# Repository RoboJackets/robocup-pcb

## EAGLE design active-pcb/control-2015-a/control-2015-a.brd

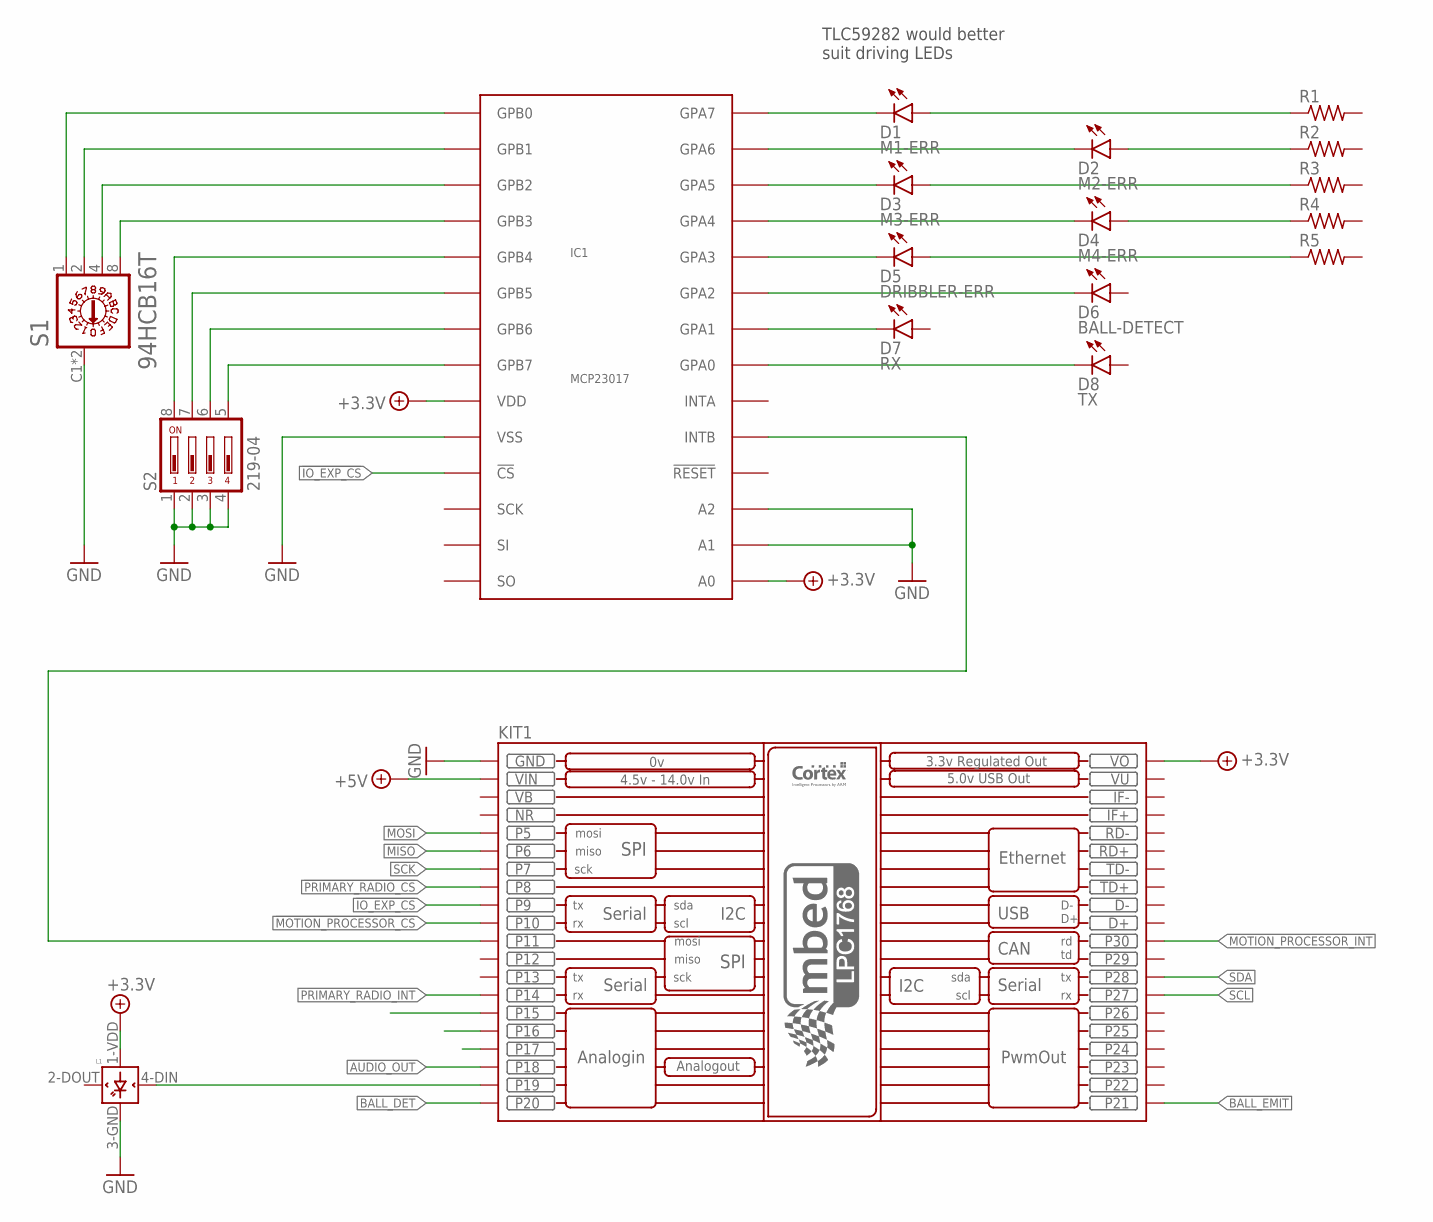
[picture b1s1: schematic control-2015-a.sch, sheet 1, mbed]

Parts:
D1: M1-ERR; LED-0603
D2: M2-ERR; LED-0603
D3: M3-ERR; LED-0603
D4: M4-ERR; LED-0603
D5: DRIBBLER-ERR; LED-0603
D6: BALL-DETECT; LED-0603
D7: RX; LED-0603
D8: TX; LED-0603
IC1: MCP23017; SSOP-28
KIT1: MBED_NXP_LPC1768; MBED-KIT
L1: WS2812B
R1, R2, R3, R4, R5: R-US_R0402; R0402
S1: 94HCB16T; HEX
S2: 219-04; CTS-219-04

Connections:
!IO_EXP_CS!: IC1.11 (!CS!), KIT1.P$9 (P9)
!MOTION_PROCESSOR_CS!: KIT1.P$10 (P10); also elsewhere on the board
!PRIMARY_RADIO_CS!: KIT1.P$8 (P8); also elsewhere on the board
+3.3V: IC1.9 (VDD), IC1.15 (A0), KIT1.VOUT (VO), L1.1-VDD (VDD); also elsewhere on the board
+5V: KIT1.VIN
AUDIO_OUT: KIT1.P$18 (P18)
BALL_DET: KIT1.P$20 (P20)
BALL_EMIT: KIT1.P$21 (P21)
GND: IC1.10 (VSS), IC1.16 (A1), IC1.17 (A2), KIT1.GND, L1.3-GND (GND), S1.C1 (C), S1.C2 (C), S2.1, S2.2, S2.3, S2.4; also elsewhere on the board
MISO: KIT1.P$6 (P6); also elsewhere on the board
MOSI: KIT1.P$5 (P5); also elsewhere on the board
MOTION_PROCESSOR_INT: KIT1.P$30 (P30); also elsewhere on the board
unnamed: IC1.19 (INTB), KIT1.P$11 (P11)
unnamed: D1.C, IC1.28 (GPA7)
unnamed: D2.C, IC1.27 (GPA6)
unnamed: D3.C, IC1.26 (GPA5)
unnamed: D4.C, IC1.25 (GPA4)
unnamed: D5.C, IC1.24 (GPA3)
unnamed: D1.A, R1.1
unnamed: D2.A, R2.1
unnamed: D3.A, R3.1
unnamed: D4.A, R4.1
unnamed: D5.A, R5.1
unnamed: D6.C, IC1.23 (GPA2)
unnamed: D7.C, IC1.22 (GPA1)
unnamed: D8.C, IC1.21 (GPA0)
unnamed: IC1.1 (GPB0), S1.1
unnamed: IC1.2 (GPB1), S1.2
unnamed: IC1.3 (GPB2), S1.4
unnamed: IC1.4 (GPB3), S1.8
unnamed: IC1.5 (GPB4), S2.8
unnamed: KIT1.P$19 (P19), L1.4-DIN (DIN)
unnamed: IC1.6 (GPB5), S2.7
unnamed: IC1.7 (GPB6), S2.6
unnamed: IC1.8 (GPB7), S2.5
NR: KIT1.NR
PRIMARY_RADIO_INT: KIT1.P$14 (P14); also elsewhere on the board
SCK: KIT1.P$7 (P7); also elsewhere on the board
SCL: KIT1.P$27 (P27); also elsewhere on the board
SDA: KIT1.P$28 (P28); also elsewhere on the board
VB: KIT1.VB
VU: KIT1.VU

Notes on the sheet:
TLC59282 would better suit driving LEDs

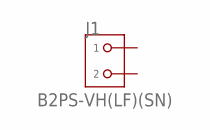
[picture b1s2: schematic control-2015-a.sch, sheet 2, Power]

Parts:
J1: B2PS-VH(LF)(SN); B2PS

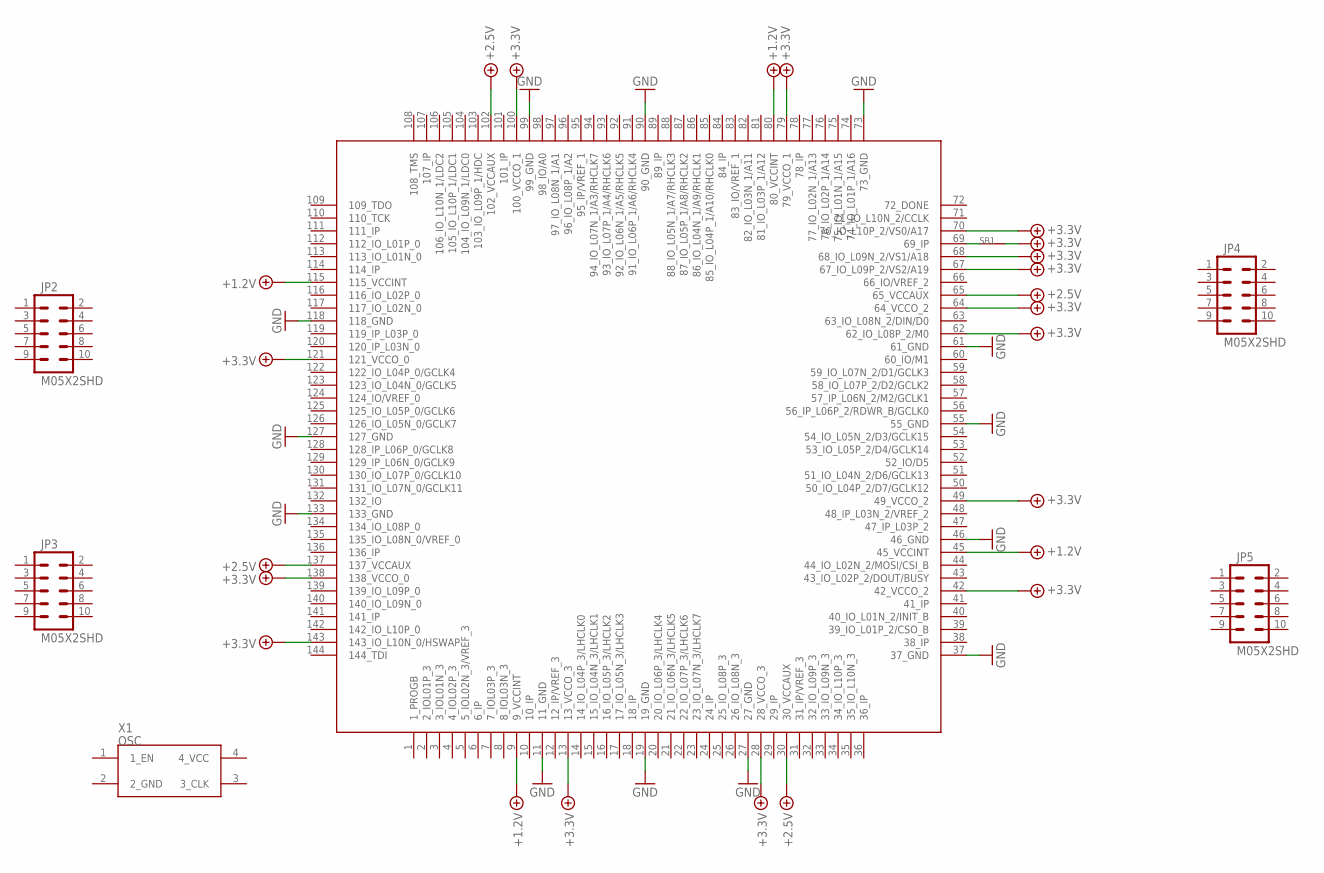
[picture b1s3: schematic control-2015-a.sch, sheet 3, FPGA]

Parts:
JP2, JP3, JP4, JP5: M05X2SHD; 2X5-SHROUDED
SB1: SOLDERBRIDGESB0603; SB0603
U$2: XC3S_TQ144; TQFP144
X1: OSC; XTAL_LCC

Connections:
+1.2V: U$2.9 (9_VCCINT), U$2.45 (45_VCCINT), U$2.80 (80_VCCINT), U$2.115 (115_VCCINT)
+2.5V: U$2.30 (30_VCCAUX), U$2.65 (65_VCCAUX), U$2.102 (102_VCCAUX), U$2.137 (137_VCCAUX)
+3.3V: SB1.2, U$2.13 (13_VCCO_3), U$2.28 (28_VCCO_3), U$2.42 (42_VCCO_2), U$2.49 (49_VCCO_2), U$2.62 (62_IO_L08P_2/M0), U$2.64 (64_VCCO_2), U$2.67 (67_IO_L09P_2/VS2/A19), U$2.68 (68_IO_L09N_2/VS1/A18), U$2.70 (70_IO_L10P_2/VS0/A17), U$2.79 (79_VCCO_1), U$2.100 (100_VCCO_1), U$2.121 (121_VCCO_0), U$2.138 (138_VCCO_0), U$2.143 (143_IO_L10N_0/HSWAP); also elsewhere on the board
GND: U$2.11 (11_GND), U$2.19 (19_GND), U$2.27 (27_GND), U$2.37 (37_GND), U$2.46 (46_GND), U$2.55 (55_GND), U$2.61 (61_GND), U$2.73 (73_GND), U$2.90 (90_GND), U$2.99 (99_GND), U$2.118 (118_GND), U$2.127 (127_GND), U$2.133 (133_GND); also elsewhere on the board
unnamed: SB1.1, U$2.69 (69_IP)

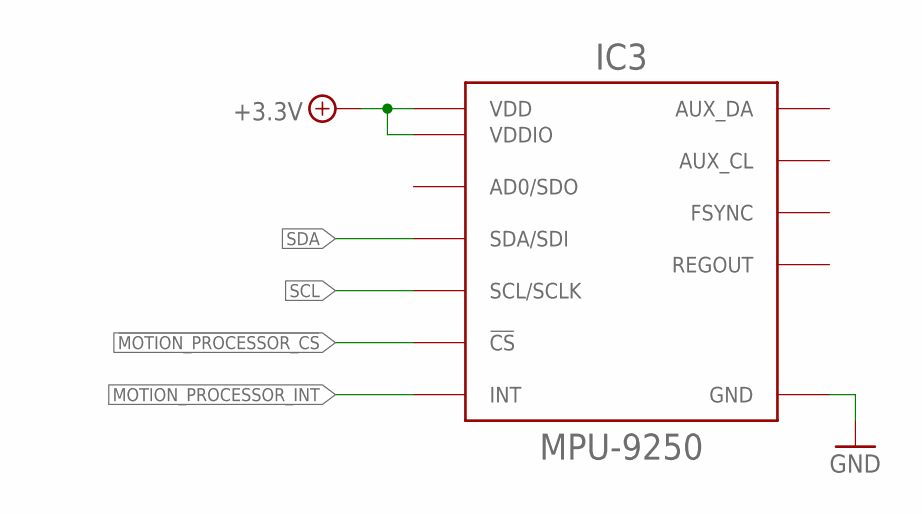
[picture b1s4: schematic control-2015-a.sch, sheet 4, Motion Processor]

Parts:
IC3: MPU-9250; QFN-24-4MM2

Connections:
!MOTION_PROCESSOR_CS!: IC3.22 (!CS!); also elsewhere on the board
+3.3V: IC3.1 (VDDIO), IC3.8 (VDDIO), IC3.13 (VDD); also elsewhere on the board
GND: IC3.18 (GND), IC3.20 (GND); also elsewhere on the board
MOTION_PROCESSOR_INT: IC3.12 (INT); also elsewhere on the board
SCL: IC3.23 (SCL/SCLK); also elsewhere on the board
SDA: IC3.24 (SDA/SDI); also elsewhere on the board

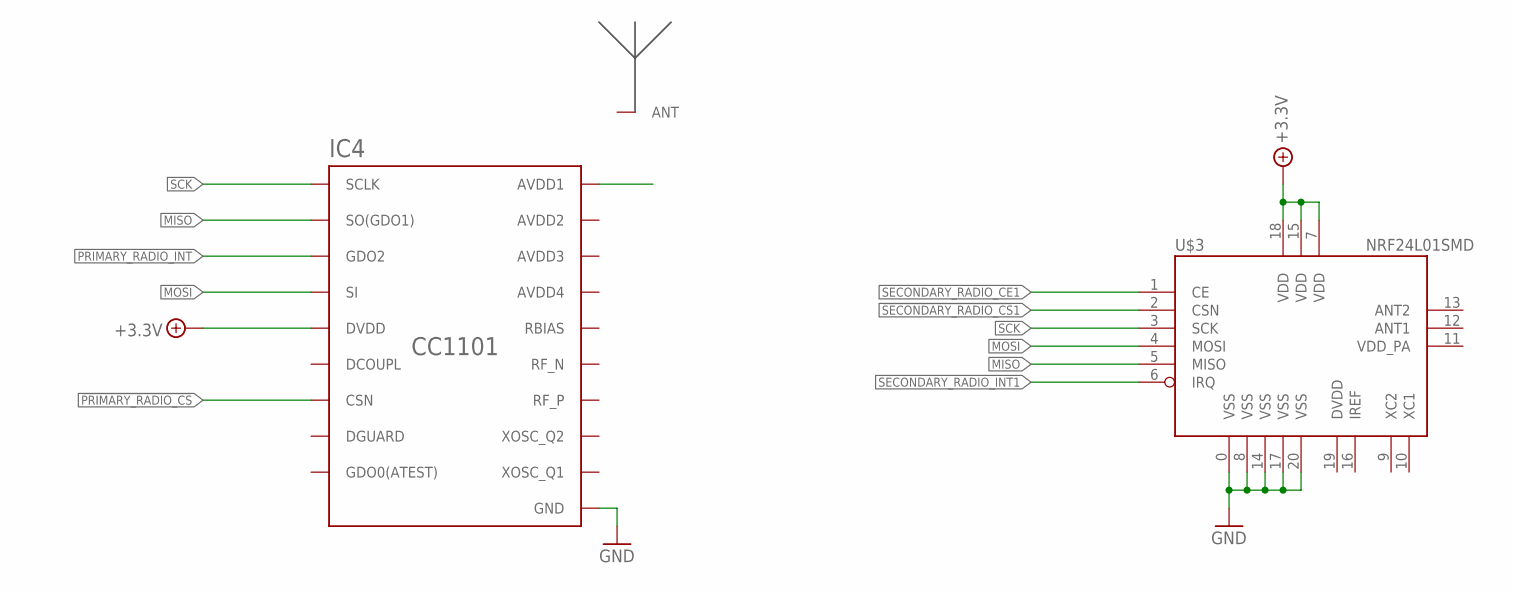
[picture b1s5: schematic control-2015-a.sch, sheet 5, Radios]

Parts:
ANT2: ANT-916-CHP-T; ANT-916-CHP
IC4: CC1101; QLP20
U$3: NRF24L01SMD; QFN20

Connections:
!PRIMARY_RADIO_CS!: IC4.7 (CSN); also elsewhere on the board
!SECONDARY_RADIO_CS!1: U$3.2 (CSN)
+3.3V: IC4.4 (DVDD), U$3.7 (VDD), U$3.15 (VDD), U$3.18 (VDD); also elsewhere on the board
DVDD: U$3.19 (DVDD)
GND: IC4.16 (GND), IC4.19 (GND), IC4.GND, IC4.GND1 (GND), IC4.GND2 (GND), IC4.GND3 (GND), IC4.GND4 (GND), IC4.GND5 (GND), U$3.0 (VSS), U$3.8 (VSS), U$3.14 (VSS), U$3.17 (VSS), U$3.20 (VSS); also elsewhere on the board
MISO: IC4.2 (SO(GDO1)), U$3.5 (MISO); also elsewhere on the board
MOSI: IC4.20 (SI), U$3.4 (MOSI); also elsewhere on the board
PRIMARY_RADIO_INT: IC4.3 (GDO2); also elsewhere on the board
SCK: IC4.1 (SCLK), U$3.3 (SCK); also elsewhere on the board
SECONDARY_RADIO_CE1: U$3.1 (CE)
SECONDARY_RADIO_INT1: U$3.6 (IRQ)
VDD_PA: U$3.11 (VDD_PA)

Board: 2 copper layers, 30 parts (2 on the bottom side), 38 nets, no tracks yet.

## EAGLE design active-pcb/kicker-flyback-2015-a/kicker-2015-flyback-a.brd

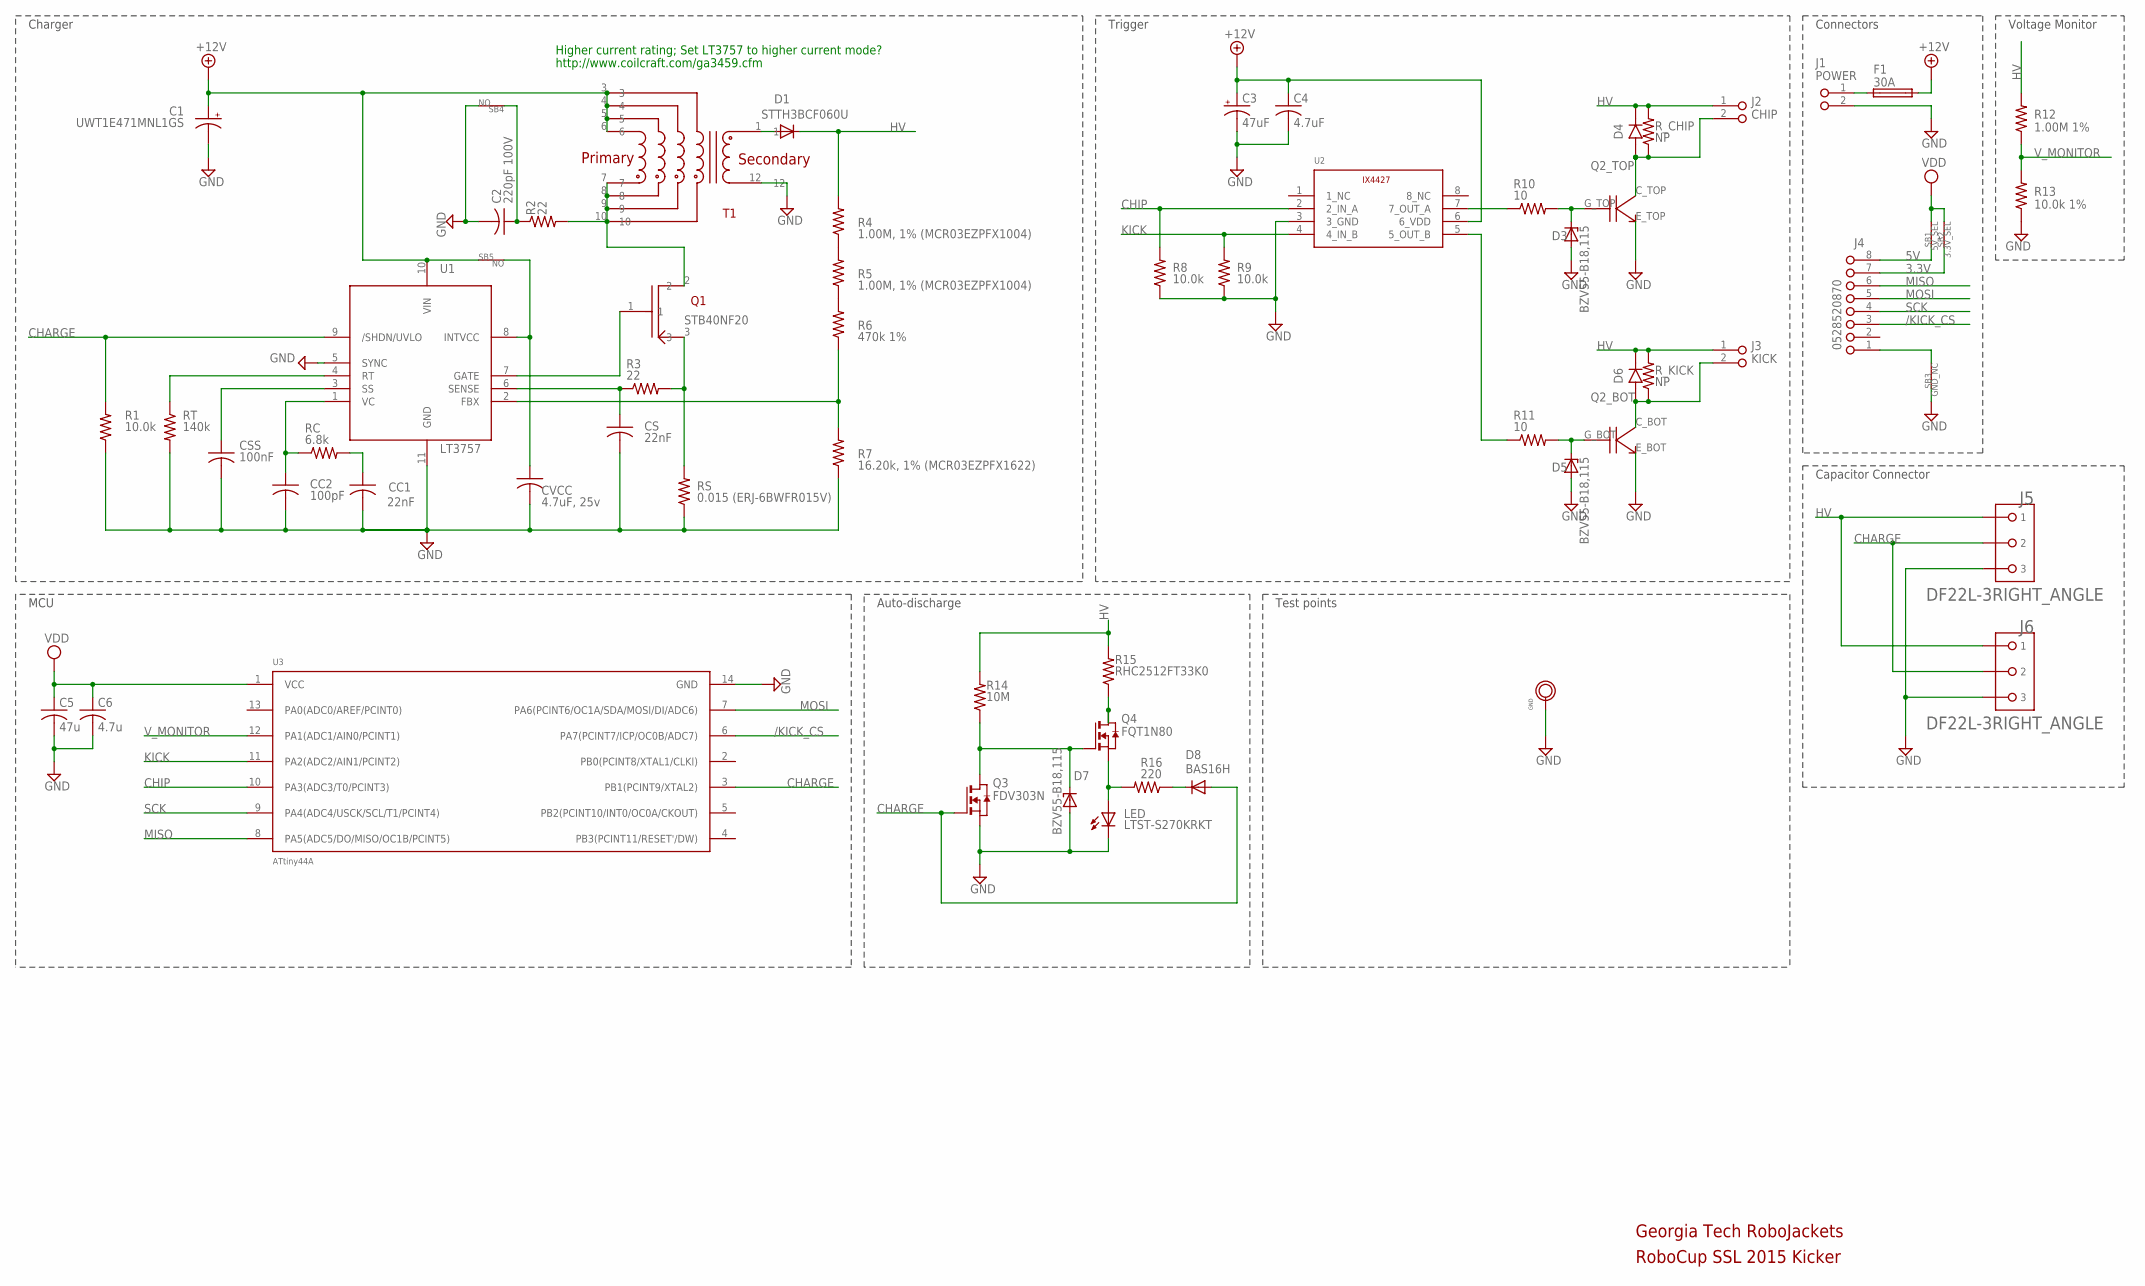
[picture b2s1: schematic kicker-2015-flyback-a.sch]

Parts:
C1: UWT1E471MNL1GS; PANASONIC_G
C2: 220pF 100V; C0603
C3: 47uF; C/6032-28R
C4: 4.7uF; C1206K
C5: 47u; C0603K
C6: 4.7u; C0603K
CC1: 22nF; C0603
CC2: 100pF; C0603
CS: 22nF; C0603
CSS: 100nF; C0603
CVCC: 4.7uF, 25v; C1206
D1: STTH3R06U; SMB
D3, D5, D7: BZV55-B18,115; SOD80C
D4, D6: S10M; DO-214AB
D8: BAS16H; SOD323-W
F1: 30A; NANO2_157
J1: POWER; JST_VH_2_RA
J2: CHIP; JST_VH_2_RA
J3: KICK; JST_VH_2_RA
J4: 0528520870
J5, J6: DF22L-3RIGHT_ANGLE; DF22L-3-H
LED: LTST-S270KRKT; CHIPLED_0603
Q1: STB40NF20; D2PACK
Q2: IXGK400N30A3_2; TO264_2
Q3: FDV303N; SOT-23
Q4: FQT1N80; SOT223
R1, R8, R9: 10.0k; R0603
R2, R3: 22; R0603
R4, R5: 1.00M, 1% (MCR03EZPFX1004); R0603
R6: 470k 1%; R0603
R7: 16.20k, 1% (MCR03EZPFX1622); R0603
R10, R11: 10; R0603
R12: 1.00M 1%; R0603
R13: 10.0k 1%; R0603
R14: 10M; R0603
R15: RHC2512FT33K0; R2512
R16: 220; R0603
RC: 6.8k; R0603
RS: 0.015 (ERJ-6BWFR015V); R0805
RT: 140k; R0603
R_CHIP: NP; R1206
R_KICK: NP; R1206
SB1: 5V_SEL; SB0603
SB2: 3.3V_SEL; SB0603
SB3: GND_NC; SB0603
SB4, SB5: NO; SB0603
T1: DA2034
TP1: GND; VIA_2MM
U1: LT3757; MSOP-10-MSE
U2: IX4427N; SOIC-8
U3: ATtiny44A; SOIC-14

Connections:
3.3V: J4.7, SB2.1
5V: J4.8, SB1.1
+12V: C1.+, C3.+, C4.1, F1.P$2 (2), SB5.1, T1.3, T1.4, T1.5, T1.6, U1.10 (VIN), U2.6 (6_VDD)
/KICK_CS: J4.3, U3.6 (PA7(PCINT7/ICP/OC0B/ADC7))
CHARGE: D8.A, J5.2, J6.2, Q3.3 (G), R1.2, U1.9 (/SHDN/UVLO), U3.3 (PB1(PCINT9/XTAL2))
CHIP: R8.2, U2.2 (2_IN_A), U3.10 (PA3(ADC3/T0/PCINT3))
HV: D1.C, D4.C, D6.C, J2.1, J3.1, J5.1, J6.1, R4.2, R12.2, R14.2, R15.2, R_CHIP.2, R_KICK.2
KICK: R9.2, U2.4 (4_IN_B), U3.11 (PA2(ADC2/AIN1/PCINT2))
MISO: J4.6, U3.8 (PA5(ADC5/DO/MISO/OC1B/PCINT5))
MOSI: J4.5, U3.7 (PA6(PCINT6/OC1A/SDA/MOSI/DI/ADC6))
unnamed: D3.C, Q2.G_TOP (G), R10.2
unnamed: Q1.1, U1.7 (GATE)
unnamed: J4.1, SB3.2
unnamed: CC2.1, RC.1, U1.1 (VC)
unnamed: CC1.1, RC.2
unnamed: R11.1, U2.5 (5_OUT_B)
unnamed: R4.1, R5.2
unnamed: D5.C, Q2.G_BOT (G), R11.2
unnamed: R5.1, R6.2
unnamed: D6.A, J3.2, Q2.C_BOT (C), R_KICK.1
unnamed: D4.A, J2.2, Q2.C_TOP (C), R_CHIP.1
unnamed: R10.1, U2.7 (7_OUT_A)
unnamed: D7.C, Q3.1 (D), Q4.1 (G), R14.1
unnamed: Q4.2 (D), Q4.4 (D2), R15.1
unnamed: F1.P$1 (1), J1.1
unnamed: CSS.1, U1.3 (SS)
unnamed: RT.1, U1.4 (RT)
unnamed: CVCC.1, SB5.2, U1.8 (INTVCC)
unnamed: LED.A, Q4.3 (S), R16.2
unnamed: CS.1, R3.1, U1.6 (SENSE)
unnamed: C2.1, R2.1, SB4.1
unnamed: D8.C, R16.1
unnamed: Q1.2, R2.2, T1.7, T1.8, T1.9, T1.10
unnamed: D1.A, T1.1
NAG: Q1.3, R3.2, RS.2
SCK: J4.4, U3.9 (PA4(ADC4/USCK/SCL/T1/PCINT4))
VDD: C5.1, C6.1, SB1.2, SB2.2, U3.1 (VCC)
VFB: R6.1, R7.2, U1.2 (FBX)
V_MONITOR: R12.1, R13.2, U3.12 (PA1(ADC1/AIN0/PCINT1))

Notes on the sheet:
RoboCup SSL 2015 Kicker
Georgia Tech RoboJackets
STTH3BCF060U
STB40NF20
Connectors
Voltage Monitor
Charger
Trigger
Auto-discharge
http://www.coilcraft.com/ga3459.cfm
Higher current rating; Set LT3757 to higher current mode?
MCU
Capacitor Connector
Test points

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
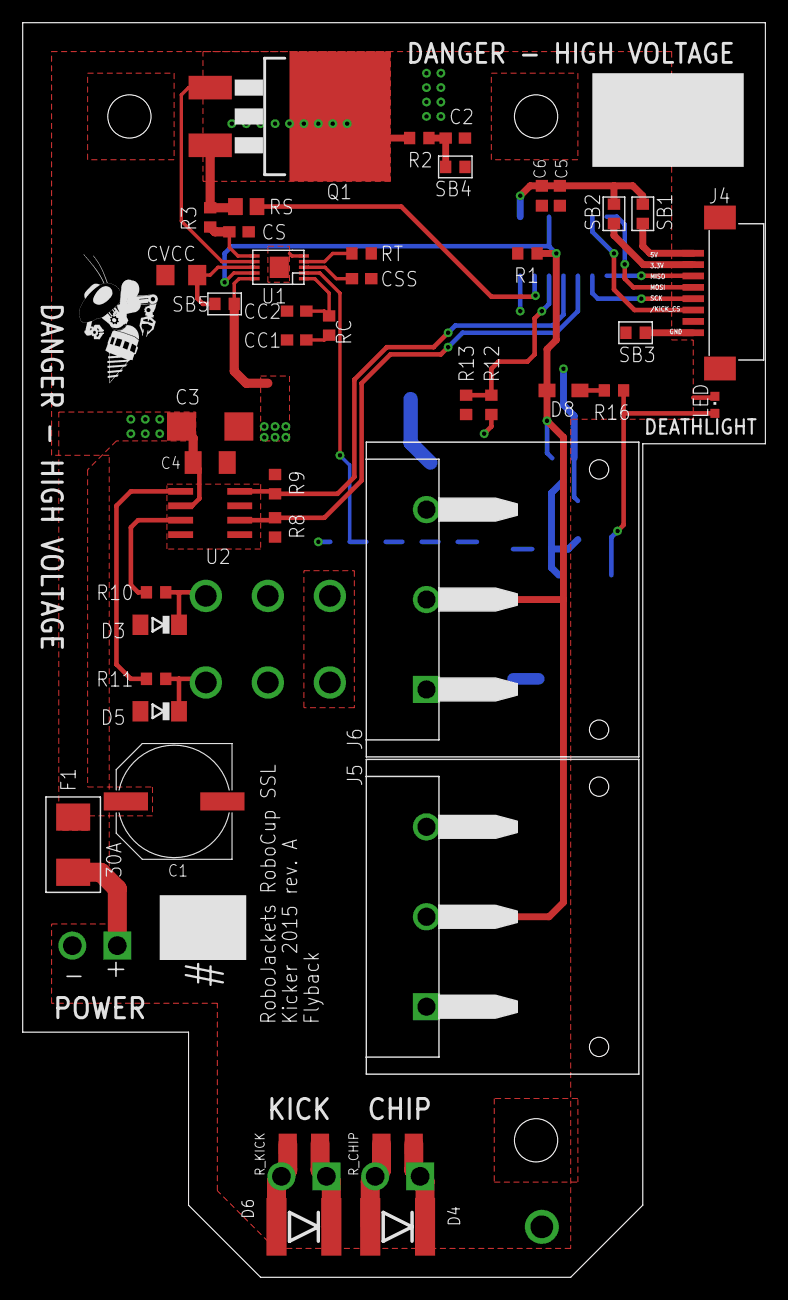
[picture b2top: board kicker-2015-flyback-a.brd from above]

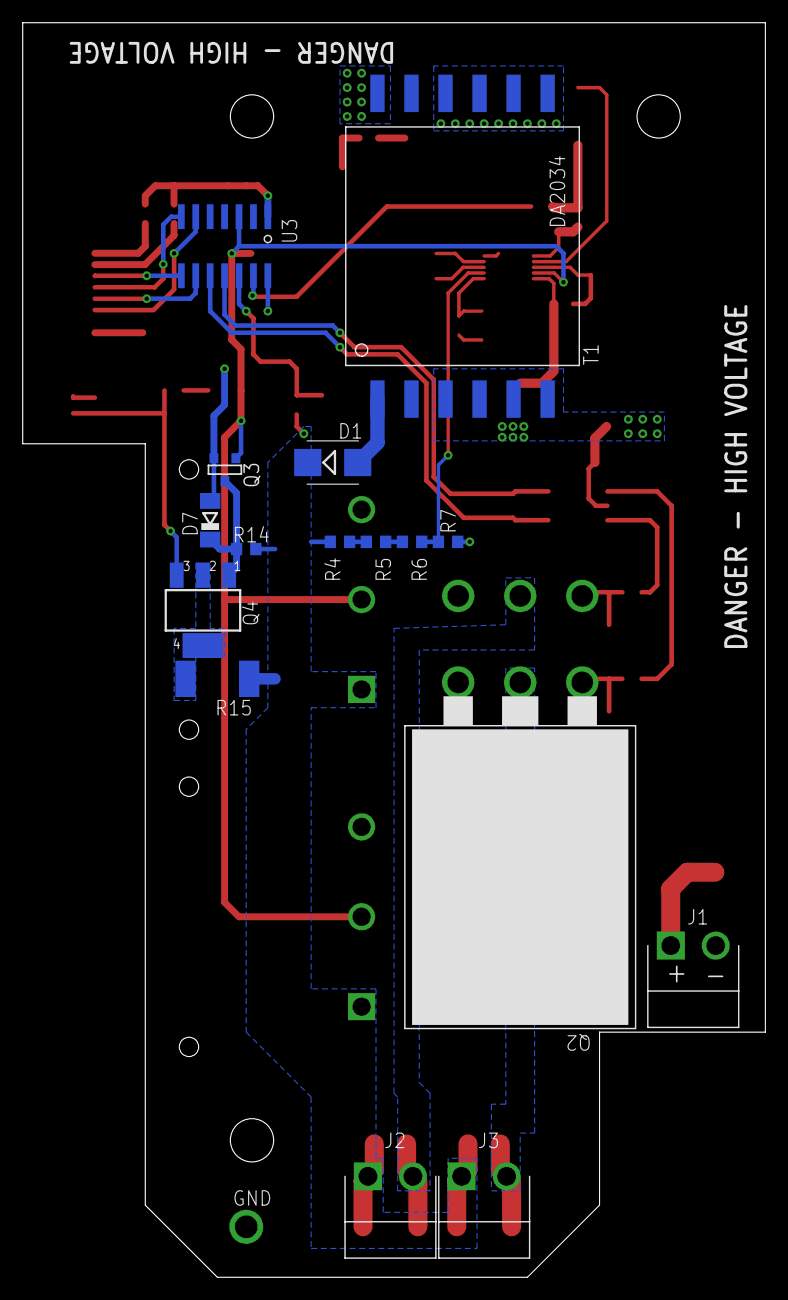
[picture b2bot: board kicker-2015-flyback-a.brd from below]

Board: 2 copper layers, 65.4 x 110.5 mm, 62 parts (16 on the bottom side), 41 nets.

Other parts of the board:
U$1: ROBOBUZZ_0.6X

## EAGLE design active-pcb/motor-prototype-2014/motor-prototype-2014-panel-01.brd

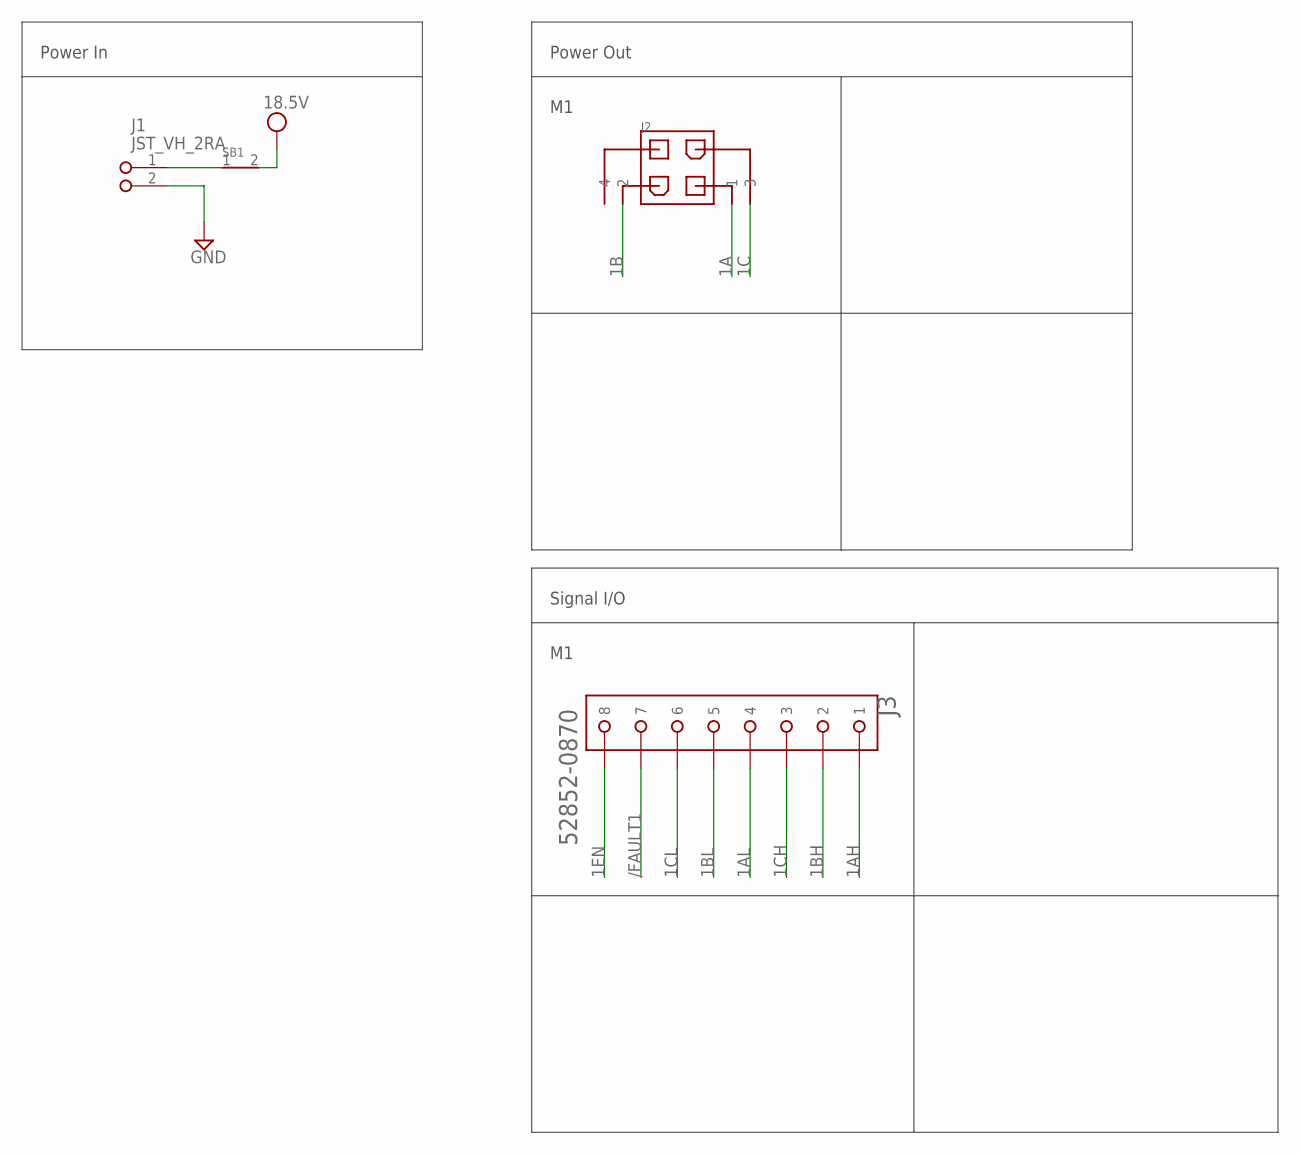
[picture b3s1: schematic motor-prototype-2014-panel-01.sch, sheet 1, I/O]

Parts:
J1: JST_VH_2RA; JST_VH_2_RA
J2: MINIFITJR_HDR_2X2; MINIFITJR_HDR_2X2_RA
J3: 52852-0870; 52852-08
SB1: SOLDERBRIDGESB1206; SB1206

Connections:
1A: J2.P$1 (1); also elsewhere on the board
1AH: J3.1; also elsewhere on the board
1AL: J3.4; also elsewhere on the board
1B: J2.P$2 (2); also elsewhere on the board
1BH: J3.2; also elsewhere on the board
1BL: J3.5; also elsewhere on the board
1C: J2.P$3 (3); also elsewhere on the board
1CH: J3.3; also elsewhere on the board
1CL: J3.6; also elsewhere on the board
1EN: J3.8; also elsewhere on the board
/FAULT1: J3.7; also elsewhere on the board
GND: J1.2; also elsewhere on the board
VCC: SB1.2; also elsewhere on the board
V_IN: J1.1, SB1.1

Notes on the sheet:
Power In
Power Out
Signal I/O

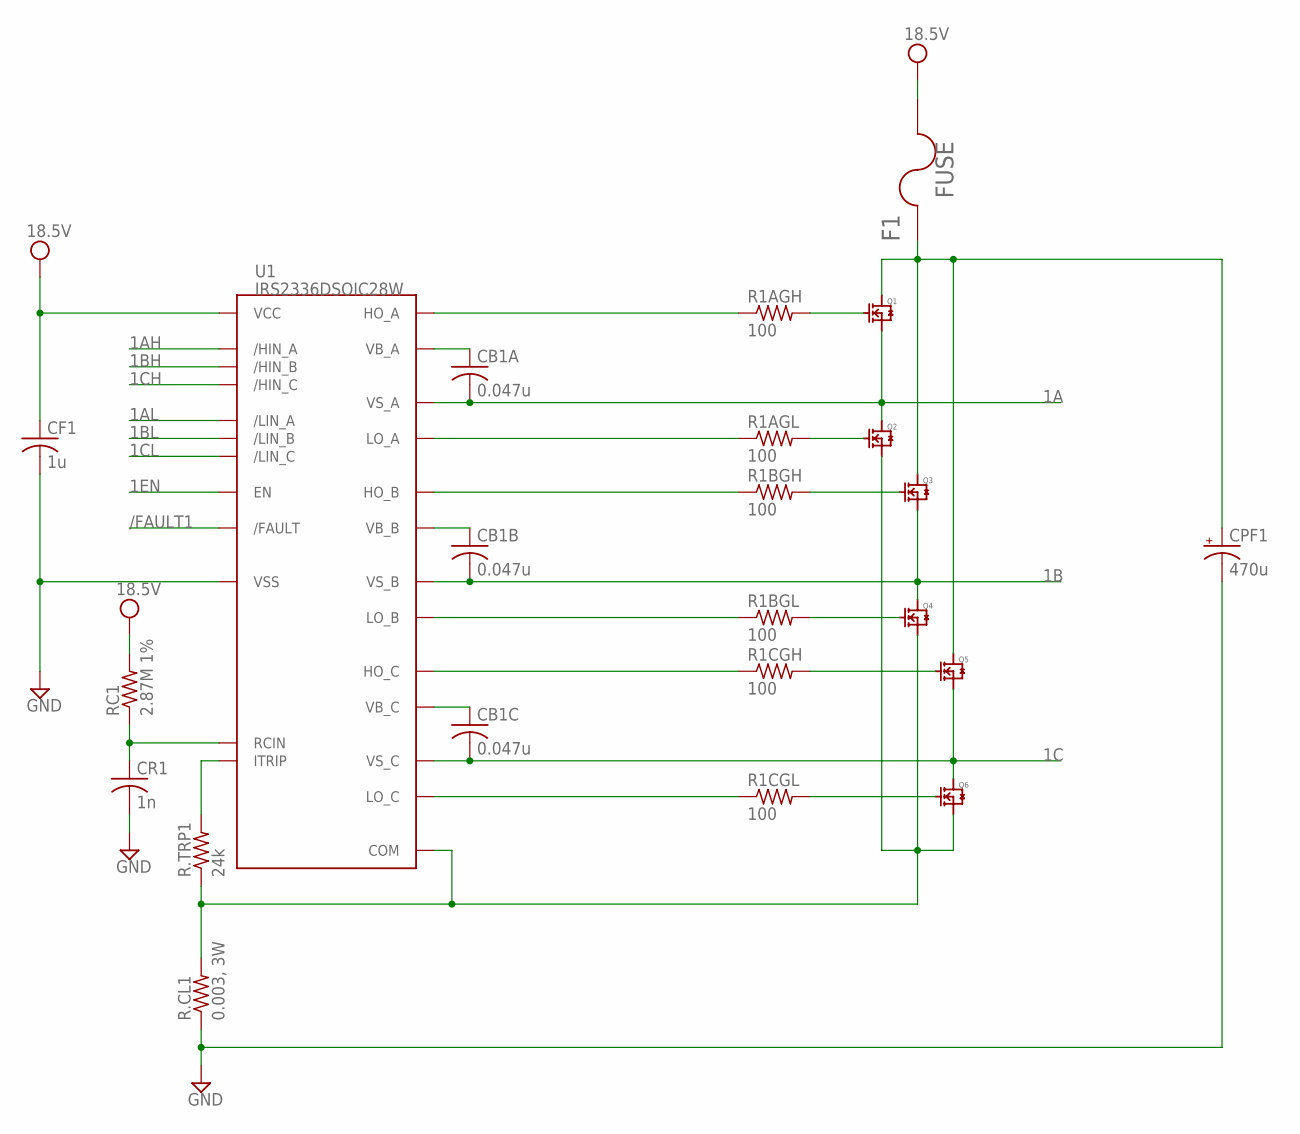
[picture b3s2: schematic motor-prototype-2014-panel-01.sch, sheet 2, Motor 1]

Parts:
CB1A, CB1B, CB1C: 0.047u; C1206
CF1: 1u; C0603
CPF1: 470u; PANASONIC_G
CR1: 1n; C0603
F1: FUSE; FUSE_MINI_ATC
Q1, Q2, Q3, Q4, Q5, Q6: SIR438DP; POWERPAK_SO8
R1AGH, R1AGL, R1BGH, R1BGL, R1CGH, R1CGL: 100; R0603
R.CL1: 0.003, 3W; R2512
R.TRP1: 24k; R0603
RC1: 2.87M 1%; R0603
U1: IRS2336DSOIC28W; SO-28W

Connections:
1A: CB1A.2, Q1.1 (S), Q1.2 (S), Q1.3 (S), Q2.5 (D), U1.26 (VS_A); also elsewhere on the board
1AH: U1.2 (/HIN_A); also elsewhere on the board
1AL: U1.5 (/LIN_A); also elsewhere on the board
1B: CB1B.2, Q3.1 (S), Q3.2 (S), Q3.3 (S), Q4.5 (D), U1.22 (VS_B); also elsewhere on the board
1BH: U1.3 (/HIN_B); also elsewhere on the board
1BL: U1.6 (/LIN_B); also elsewhere on the board
1C: CB1C.2, Q5.1 (S), Q5.2 (S), Q5.3 (S), Q6.5 (D), U1.18 (VS_C); also elsewhere on the board
1CH: U1.4 (/HIN_C); also elsewhere on the board
1CL: U1.7 (/LIN_C); also elsewhere on the board
1EN: U1.10 (EN); also elsewhere on the board
/FAULT1: U1.8 (/FAULT); also elsewhere on the board
GND: CF1.2, CPF1.-, CR1.2, R.CL1.1, U1.12 (VSS); also elsewhere on the board
unnamed: R1AGH.1, U1.27 (HO_A)
unnamed: Q1.4 (G), R1AGH.2
unnamed: Q2.4 (G), R1AGL.2
unnamed: R1AGL.1, U1.16 (LO_A)
unnamed: R1BGH.1, U1.23 (HO_B)
unnamed: R1BGL.1, U1.15 (LO_B)
unnamed: R1CGL.1, U1.14 (LO_C)
unnamed: R1CGH.1, U1.19 (HO_C)
unnamed: Q3.4 (G), R1BGH.2
unnamed: Q5.4 (G), R1CGH.2
unnamed: Q6.4 (G), R1CGL.2
unnamed: Q4.4 (G), R1BGL.2
unnamed: CR1.1, RC1.1, U1.11 (RCIN)
unnamed: R.TRP1.2, U1.9 (ITRIP)
PGND_1: Q2.1 (S), Q2.2 (S), Q2.3 (S), Q4.1 (S), Q4.2 (S), Q4.3 (S), Q6.1 (S), Q6.2 (S), Q6.3 (S), R.CL1.2, R.TRP1.1, U1.13 (COM)
VB_1A: CB1A.1, U1.28 (VB_A)
VB_1B: CB1B.1, U1.24 (VB_B)
VB_1C: CB1C.1, U1.20 (VB_C)
VCC: CF1.1, F1.2.1 (2), F1.2.2 (2), RC1.2, U1.1 (VCC); also elsewhere on the board
VM1: CPF1.+, F1.1.1 (1), F1.1.2 (1), Q1.5 (D), Q3.5 (D), Q5.5 (D)

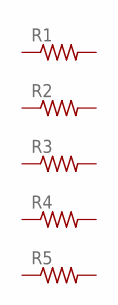
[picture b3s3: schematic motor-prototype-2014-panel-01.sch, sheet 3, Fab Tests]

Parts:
R1: R-US_R0201; R0201
R2: R-US_R0402; R0402
R3: R-US_R0603; R0603
R4: R-US_R0805; R0805
R5: R-US_R1206; R1206

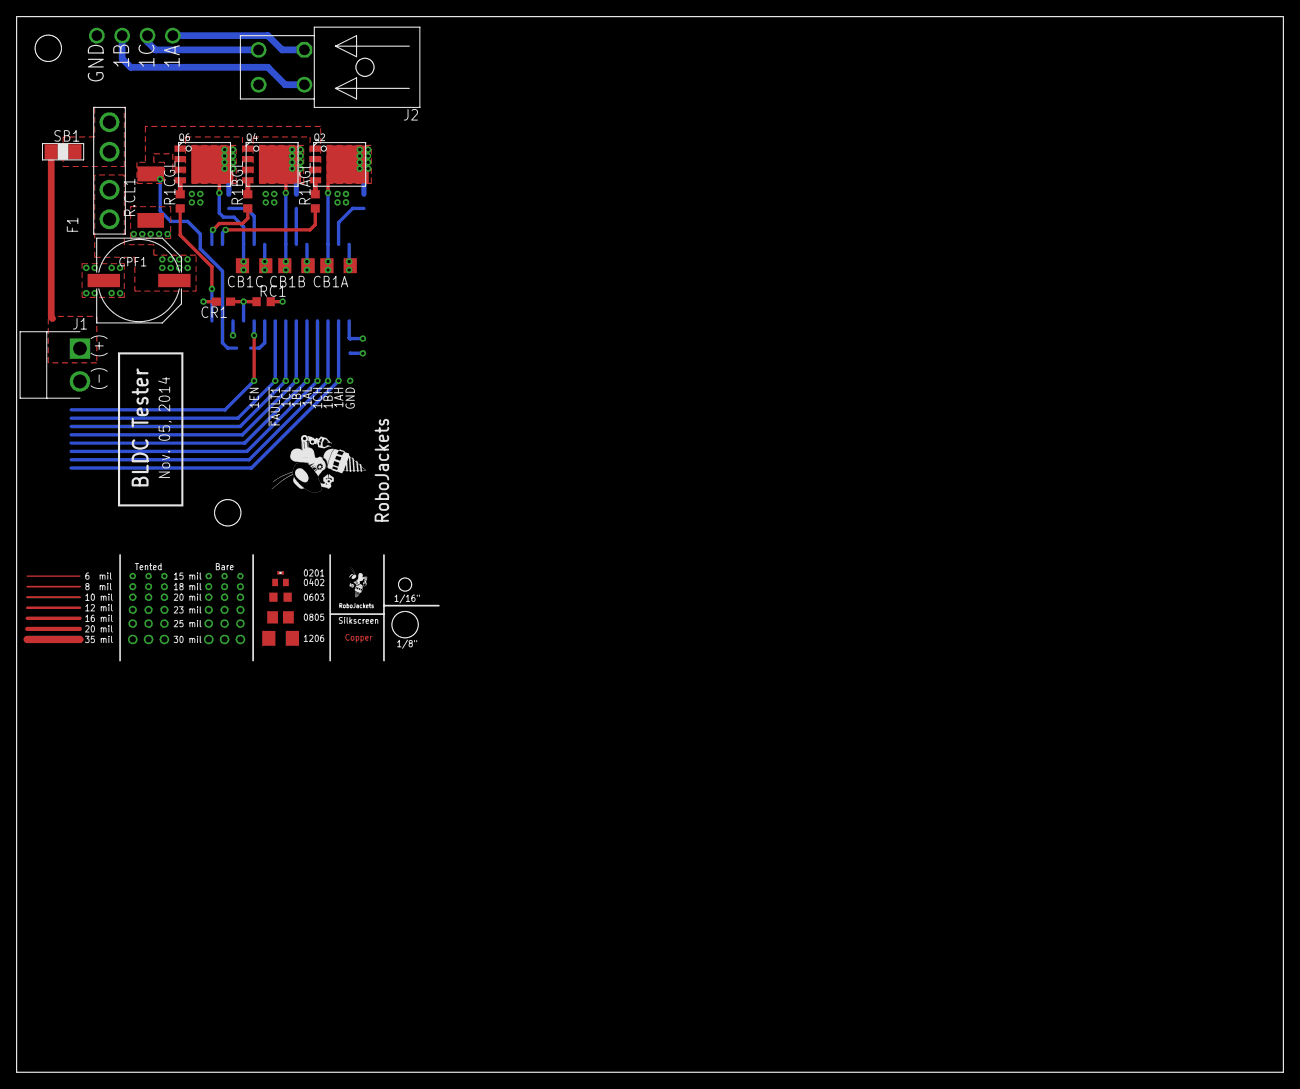
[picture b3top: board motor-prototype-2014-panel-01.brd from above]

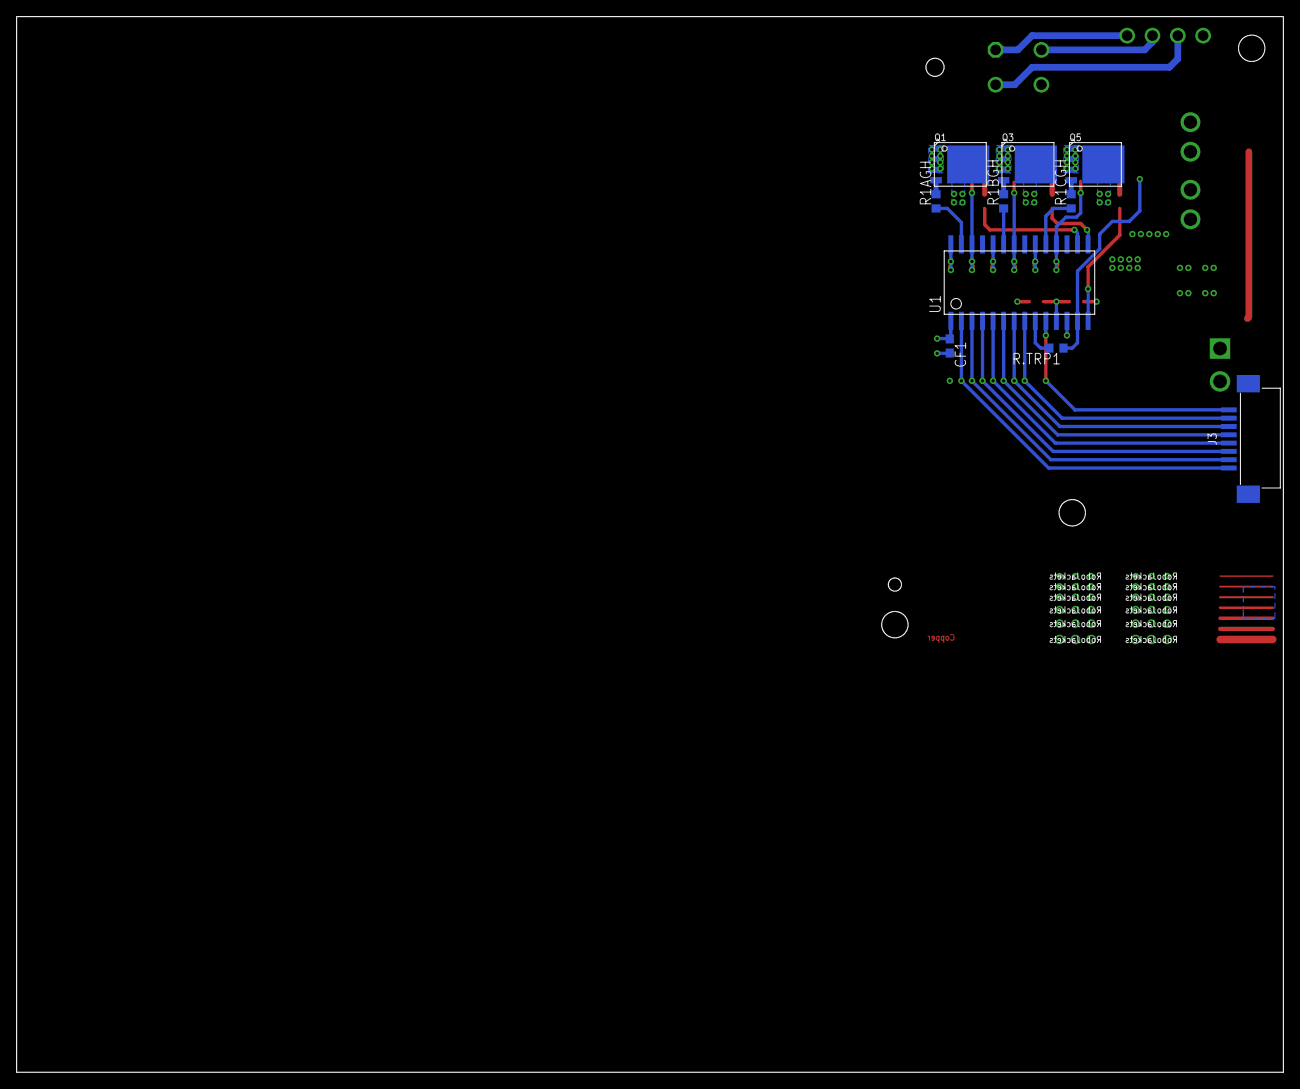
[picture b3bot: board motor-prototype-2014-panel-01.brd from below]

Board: 4 copper layers, 152.4 x 127.0 mm, 34 parts (10 on the bottom side), 33 nets.

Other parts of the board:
U$1: ROBOBUZZ_0.6X
U$3: ROBOBUZZ_0.2X

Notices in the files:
parts and their libraries:
SparkFun-LED: Licensing: Creative Commons ShareAlike 4.0 International - https://creativecommons.org/licenses/by-sa/4.0
